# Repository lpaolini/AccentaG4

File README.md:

# AccentaG4
Virtual keypad for Honeywell Security Accenta G4 panel.

## Introduction
[Accenta G4](https://www.security.honeywell.com/uk/products/intruder/control-panels/gen4/) is a simple, reliable, affordable intruder alarm panel made by *Honeywell Security*.

It works very well for residential use but, clearly, it’s not designed for extension. You cannot expand zones, you can’t operate it remotely with your smartphone, it doesn’t expose a standard serial interface to play with.

Recently, I started dreaming of a more sophisticated panel, and after thinking of a possible upgrade, I decided to hack mine.

After a bit of googling, I found a blog with a couple of interesting posts ([this](https://inmachinablog.wordpress.com/2015/11/04/accenta-alarm-keypad-protocol/) and [this](https://inmachinablog.wordpress.com/2015/11/03/decoding-the-alarm-keypad-protocol/)) providing useful background on the protocol and signalling used on the keypad bus, along with a description of the messages exchanged between the keypad and the panel.

## Keypad bus

The keypads (in [LED](https://www.security.honeywell.com/uk/products/intruder/control-panels/gen4/462382.html) and [LCD](https://www.security.honeywell.com/uk/products/intruder/control-panels/gen4/462383.html) variants) communicate with the panel over a single wire (half-duplex, shared bus) using TTL levels (+5v low, 0v high). A quick analysis with the logic analyzer revealed a slightly unusual protocol: RS-232 with 8 bit of data, *mark/space parity* and 1 stop bit or, if you prefer, *9 bit* of data and 1 stop bit, which is the same. In fact, considering bits are sent LSB first (little-endian), the parity bit is just the 9th bit of data.

Any message is sent over the bus with mark parity on the first byte and space parity on the remaining bytes.

## Messaging protocol

Luckily, all communication between panel and keypads is not encrypted nor obfuscated. In fact, the protocol is fairly straightforward.
Any message consists of a single byte command, one or more bytes of data and a one-byte checksum of all the preceding bytes.
Messages are not terminated.
```
<command> <data> [<data>...] <checksum>
```
### Messages sent by the keypad

Apparently, the keypad sends just one type of command over the bus:
```
K <keycode> <checksum>
```
The “K” character, being the first byte of the message, has mark parity.

\<keycode\> is the code representing a physical or virtual (key combination) button on the keypad:

| code | ASCII | type     | button  |
| ---- | :---: | -------- | :-----: |
| 0x30 | 0     | physical | 0       |
| 0x31 | 1     | physical | 1       |
| 0x32 | 2     | physical | 2       |
| 0x33 | 3     | physical | 3       |
| 0x34 | 4     | physical | 4       |
| 0x35 | 5     | physical | 5       |
| 0x36 | 6     | physical | 6       |
| 0x37 | 7     | physical | 7       |
| 0x38 | 8     | physical | 8       |
| 0x39 | 9     | physical | 9       |
| 0x3a | :     | physical | chime   |
| 0x3b | ;     | physical | omit    |
| 0x3c | <     | physical | cancel  |
| 0x3d | =     | physical | program |
| 0x3e | >     | physical | confirm |
| 0x3f | ?     | physical | select  |
| 0xaa | n/a   | virtual  | panic   |

### Messages sent by the panel

The panel sends out one or more messages whenever it needs to update the status displayed on the keypads. Messages of a given type are sent only if they differ from the previous message of the same type.

Please note some responses are sent exclusively as audible tones, delivered as analogue signals via a separate keypad bus wire labeled *SOUNDS*.

#### Messages for the LED keypad (P)

Whenever the status of at least one of the LEDs needs to be updated, a new message is sent.
Each message is a *full* representation of all the LEDs on the keypad.
```
P <zone info> <general info> <checksum>
```
The “P” character, being the first byte of the message, has mark parity.

\<zone info\> is a byte where each bit represents one zone LED:

| bit | LED |
| :-: | --- |
| 0   | zone 1 |
| 1   | zone 2 |
| 2   | zone 3 |
| 3   | zone 4 |
| 4   | zone 5 |
| 5   | zone 6 |
| 6   | zone 7 |
| 7   | zone 8 |

\<general info\> is a byte encoded like follows:

| bit | LED |
| :-: | --- |
| 0   | system unset |
| 1   | tamper |
| 2   | SOS |
| 3   | power |
| 4   | not used? |
| 5   | not used? |
| 6   | not used? |
| 7   | not used? |

#### Messages for the LCD keypad (L)

Whenever the text displayed on the LCD needs to be updated a new message is sent:
```
L <lenght> <LCD data> <checksum>
```
The “L” character, being the first byte of the message, has mark parity.

Lenght information is necessary, as messages are not terminated and size is not fixed, thus the receiver needs to know the message size upfront.

LCD data is a sequence of bytes, either printable (ASCII) or control codes, mostly for managing the cursor:

| code | function |
| ---- | -------- |
| 0x04 | cursor position |
| 0x05 | hide cursor |
| 0x06 | show cursor |
| 0x07 | move cursor right |
| 0x0a | newline |
| 0x0c | clear |
| 0x10 | unknown |
| 0x16 | unknown | 

Cursor position is determined by the subsequent byte:

| position | coordinates |
| -------- | ----------- |
| 0x80 to 0x8f | top row, column 1 to 16 |
| 0xc0 to 0xcf | bottom row, column 1 to 16 |

I believe the LCD keypad consumes "P" messages as well, as information regarding the status of the *power* and *day* LEDs doesn't seem to be show up anywhere in "L" messages.

## To parity or not to parity…

As said, in little-endian, 8-bit with parity and 9-bit without parity are equivalent.

In particular, 8-bit with mark parity is equivalent to 9-bit without parity when the 8-bit character is *OR*ed with 0x100.

So, it’s perfectly equivalent to forget about parity and simply think of alternate codes for the head of the message, with the 9th (or parity) bit set to 1:

| command | keycode | 9-bit code |
| :-----: | :-----: | :--------: |
| K       | 0x4b    | 0x14b      |
| L       | 0x4c    | 0x14c      |
| P       | 0x50    | 0x150      |

No matter how you look at it, having the 9th bit set exclusively for the head of the message is quite convenient, as it makes the code at the receiving end simpler and more robust. In fact it's possible to detect the head of the message without any ambiguity.

## Hardware signals

Keypad bus aside, the panel board exposes also a few output signals representing the general status, for use with a digital communicator or a speech dialer. They are labelled as follows:

- FIRE (fire)
- PA (panic)
- INT (intruder)
- SET (alarm set)
- ABORT (alarm aborted)

Signals are held at +13v and fall to 0v when active.
They are absolutely crucial for this project as some critical alert conditions (like *intruder* or *PA*) are not reflected in LED or LCD status.

## The project

The objective of this project is to build a keypad emulator running in a standard browser.

# Hardware stack

## Linux MPU: [Raspberry Pi 3+](https://www.raspberrypi.org/products/raspberry-pi-3-model-b-plus/)

The MPU is responsible for the following tasks:

- expose a HTTPS server for serving the web application
- expose a secure websockets server (used by the web application)
- accept and manage websockets connections
- listen to MCU for incoming messages and broadcast to websockets clients
- listen to websockets clients for incoming messages and forward to MCU
- send email notifications

[Server-side code](src/mpu/server) is written in Javascript and runs under latest NodeJS and depends on [express](https://github.com/expressjs/express) [serialport](https://github.com/serialport/node-serialport), [ws](https://github.com/websockets/ws) and [rxjs](https://github.com/ReactiveX/rxjs)

[Client-side code](src/mpu/client) is a HTML5/CSS3/Javascript application running in the browser.

## Arduino MCU: [Watterott RPI-UNO-HAT](https://learn.watterott.com/hats/rpi-uno-hat/)

[RPI-UNO-HAT](https://shop.watterott.com/RPi-UNO-HAT-Raspberry-Pi-Arduino-Erweiterung_1) is a very nice Raspberry Pi HAT fully compatible with Arduino UNO. It features standard headers and serial communication between Raspberry Pi and Arduino, so it's possible to program and reset the Atmel MCU from the Raspberry.

In practice, Raspberry Pi + RPI-UNO-HAT = **Arduino Yún on steroids**!

The MCU is responsible for the following tasks:

- monitor Accenta G4 panel hardware signals (PA, INT, SET, ABORT), update local state and send updates to MPU
- provide bidirectional serial connectivity with Accenta G4 keypad bus
- listen to the keypad bus for incoming messages, update local state and send updates to MPU
- listen to MPU for virtual keystrokes and send emulated keypad messages over the keypad bus
- listen to MPU for status queries and send local status
- reply to heartbeat messages to be broadcasted to the clients, to prove end-to-end connection is alive

[Arduino code](src/mcu/HomeControl) is written in C/C++ and it's built around the [SoftwareSerial9](https://github.com/lpaolini/SoftwareSerial9) library, capable of sending and receiving 9-bit messages, and [QueueArray](http://playground.arduino.cc/Code/QueueArray), a FIFO library used for enqueuing and throttling outgoing commands.

**WARNING**: the original version of SoftwareSerial9 by [addible](https://github.com/addibble/SoftwareSerial9) had a bug in the recv() method, fixed by [edreanernst](https://github.com/edreanernst/SoftwareSerial9) in his fork, then fixed by addible too. Both work fine, just make sure to use the latest version.

## Custom hardware

Interfacing the panel with Arduino is pretty simple.

In theory, two digital I/O pins and a diode is all you need for connecting the single-wire keypad bus to distinct RX and TX ports.

In practice, adding an additional resistor and a zener diode is a safe choice for limiting voltage and current across Arduino's I/O pins.

Panel signals (SET, ABORT, INT, PA) are active-low (12v on, 0v on). If Arduino's input is configured as INPUT_PULLUP, a diode is enough to pull the input down to LOW logical level when the corresponding panel output is active (LOW).

However, the keypad bus might be tampered with or be subject to interferences potentially harmful to Arduino. For these reasons, I have designed an opto-isolated circuit which provides full electrical isolation between Arduino and the panel itself.

 keypad bus and panel signals interface")

The circuit is designed to keep the opto-isolator LEDs off during standby, to maximize their life expectancy. 
Here is a short description of the resistors:

|Resistor|Description|
|:------:|-----------|
|R1      |limit the current into the transmitting opto-isolator LED|
|R2      |limit the current into the transmitting opto-isolator transistor|
|R3      |limit the current into the receiving opto-isolator transistor|
|R4      |limit the current into the receiving opto-isolator LED|
|R5      |set the saturation current for T2|
|R6      |set the saturation current for T1|

TO BE CONTINUED...

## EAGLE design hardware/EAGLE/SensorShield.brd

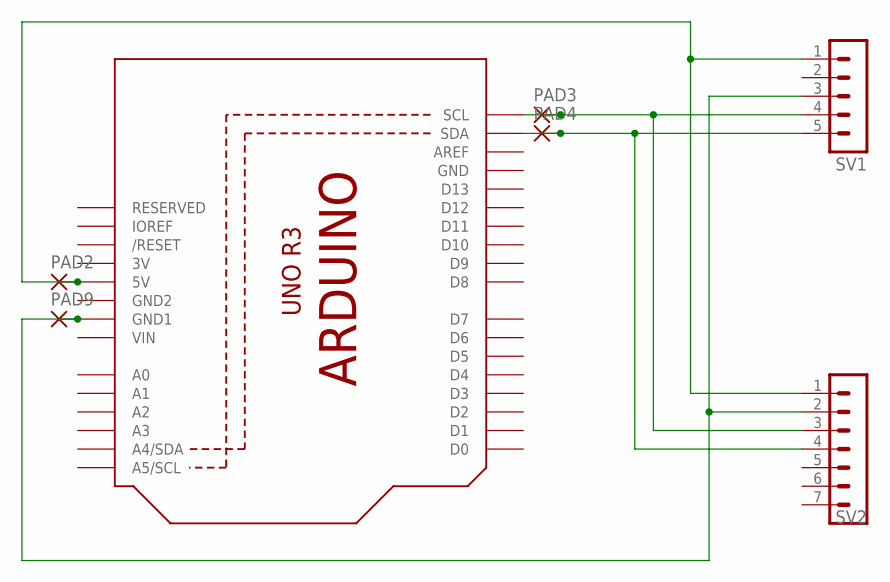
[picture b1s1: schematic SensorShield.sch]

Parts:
PAD2, PAD3, PAD4, PAD9: 1,6/0,8
SV1: MA05-1
SV2: MA07-1
U1: ARDUINOR3-BPLACE

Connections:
3V: U1.3V
GND: U1.GND
GND2: U1.GND2
unnamed: PAD9.1, SV1.3, SV2.2, U1.GND1
unnamed: PAD3.1, SV1.4, SV2.3, U1.SCL
unnamed: PAD4.1, SV1.5, SV2.4, U1.SDA
unnamed: PAD2.1, SV1.1, SV2.1, U1.5V
VIN: U1.VIN

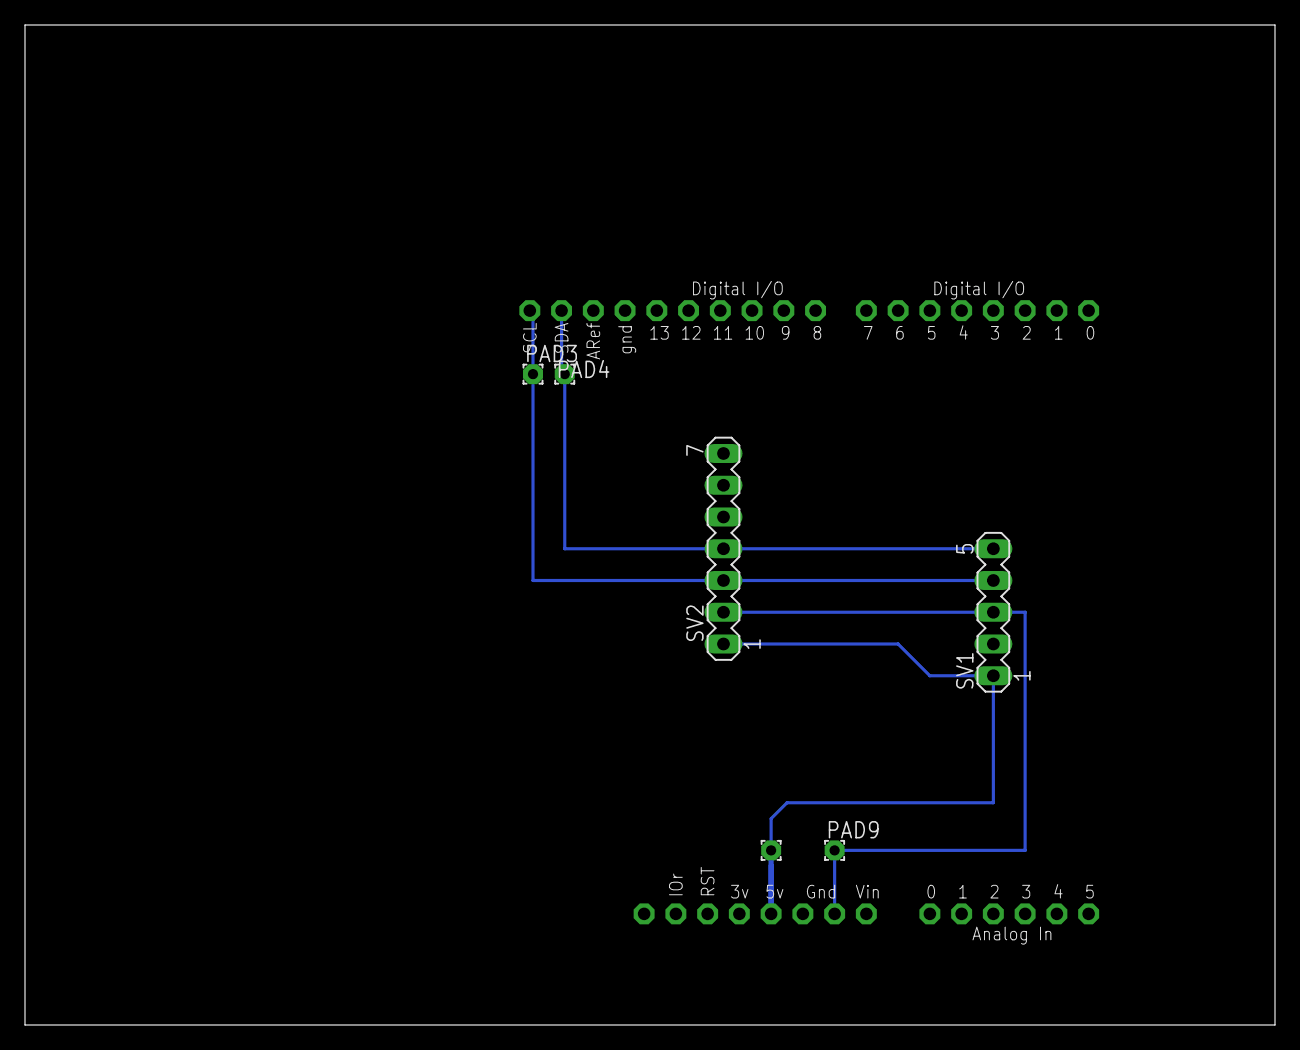
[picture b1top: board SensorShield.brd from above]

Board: 2 copper layers, 100.0 x 80.0 mm, 7 parts (0 on the bottom side), 4 nets.

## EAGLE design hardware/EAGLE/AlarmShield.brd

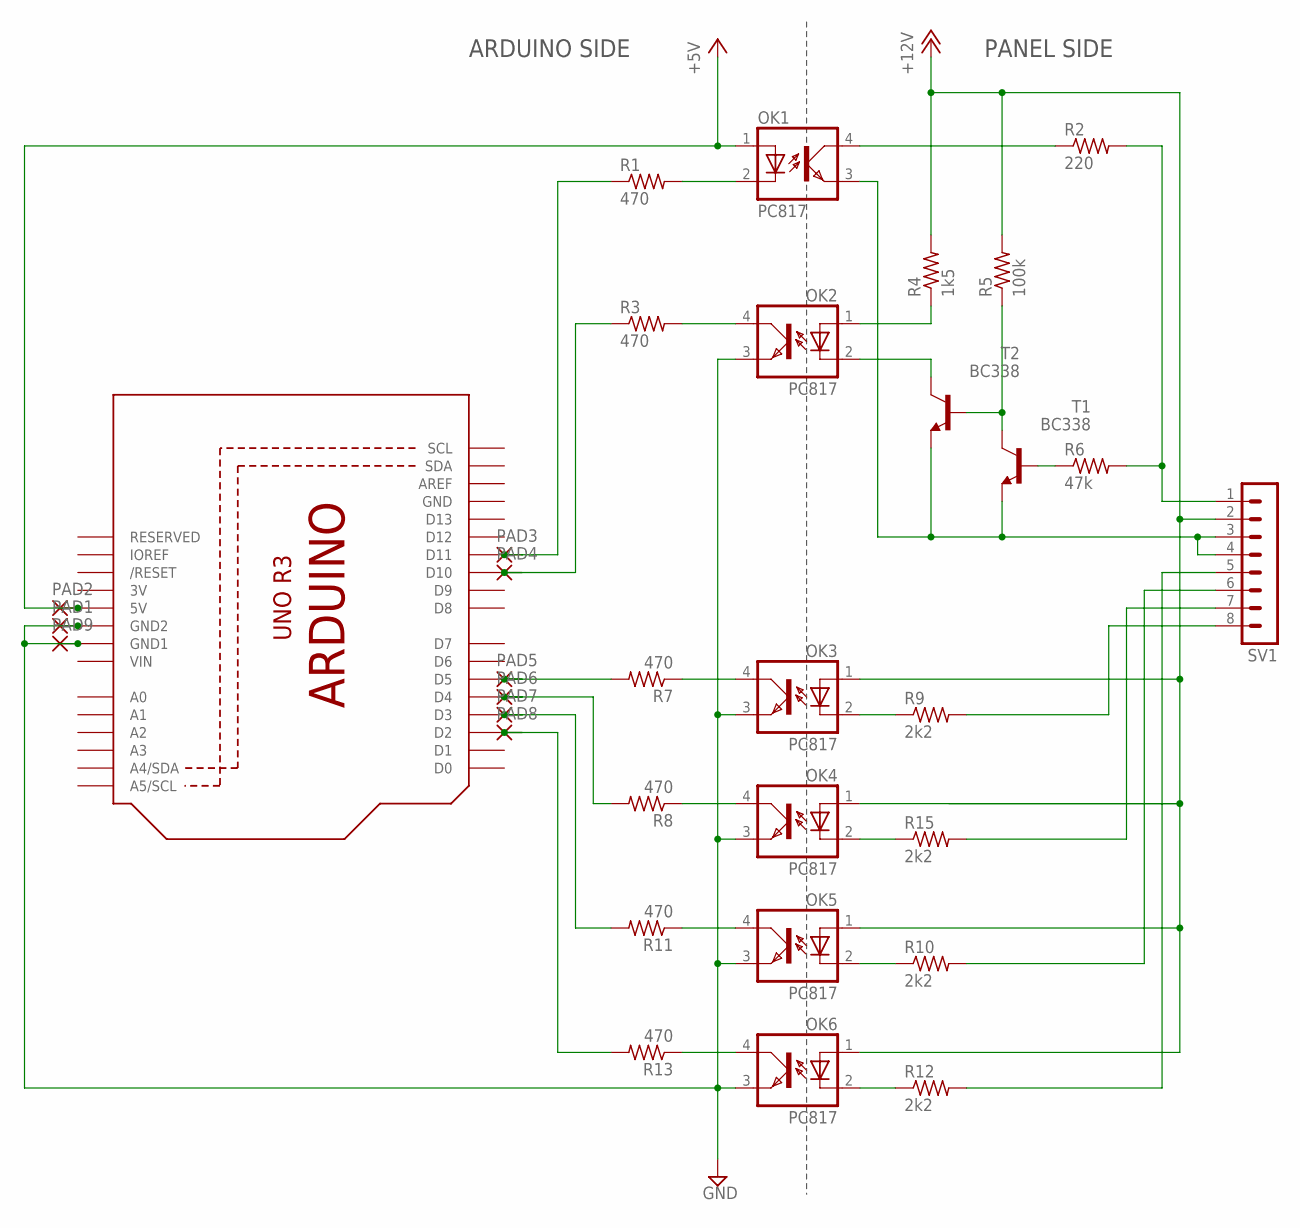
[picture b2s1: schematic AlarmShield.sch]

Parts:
OK1, OK2, OK3, OK4, OK5, OK6: PC817; DIP4
PAD1, PAD2, PAD3, PAD4, PAD5, PAD6, PAD7, PAD8, PAD9: 1,6/0,8
R1, R3, R7, R8, R11, R13: 470; 0207/10
R2: 220; 0207/10
R4: 1k5; 0207/10
R5: 100k; 0207/10
R6: 47k; 0207/10
R9, R10, R12, R15: 2k2; 0207/10
SV1: MA08-1
T1, T2: BC338; TO92-EBC
U1: ARDUINOR3-BPLACE

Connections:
3V: U1.3V
+5V: OK1.1 (A), PAD2.1, U1.5V
+12V: OK3.1 (A), OK4.1 (A), OK5.1 (A), OK6.1 (A), R4.2, R5.2, SV1.2
GND: U1.GND
GND1: OK2.3 (EMIT), OK3.3 (EMIT), OK4.3 (EMIT), OK5.3 (EMIT), OK6.3 (EMIT), PAD1.1, PAD9.1, U1.GND1, U1.GND2
unnamed: OK1.2 (C), R1.2
unnamed: OK1.3 (EMIT), SV1.3, SV1.4, T1.E, T2.E
unnamed: OK1.4 (COL), R2.1
unnamed: OK3.4 (COL), R7.1
unnamed: OK4.4 (COL), R8.1
unnamed: OK2.1 (A), R4.1
unnamed: OK2.2 (C), T2.C
unnamed: R5.1, T1.C, T2.B
unnamed: PAD3.1, R1.1, U1.D11
unnamed: R6.1, T1.B
unnamed: OK5.4 (COL), R11.1
unnamed: PAD5.1, R7.2, U1.D5
unnamed: OK6.4 (COL), R13.1
unnamed: OK2.4 (COL), R3.2
unnamed: PAD6.1, R8.2, U1.D4
unnamed: PAD7.1, R11.2, U1.D3
unnamed: PAD4.1, R3.1, U1.D10
unnamed: R2.2, R6.2, SV1.1
unnamed: R9.2, SV1.8
unnamed: R15.2, SV1.7
unnamed: OK4.2 (C), R15.1
unnamed: PAD8.1, R13.2, U1.D2
unnamed: R10.2, SV1.6
unnamed: OK3.2 (C), R9.1
unnamed: R12.2, SV1.5
unnamed: OK5.2 (C), R10.1
unnamed: OK6.2 (C), R12.1
VIN: U1.VIN

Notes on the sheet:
PANEL SIDE
ARDUINO SIDE

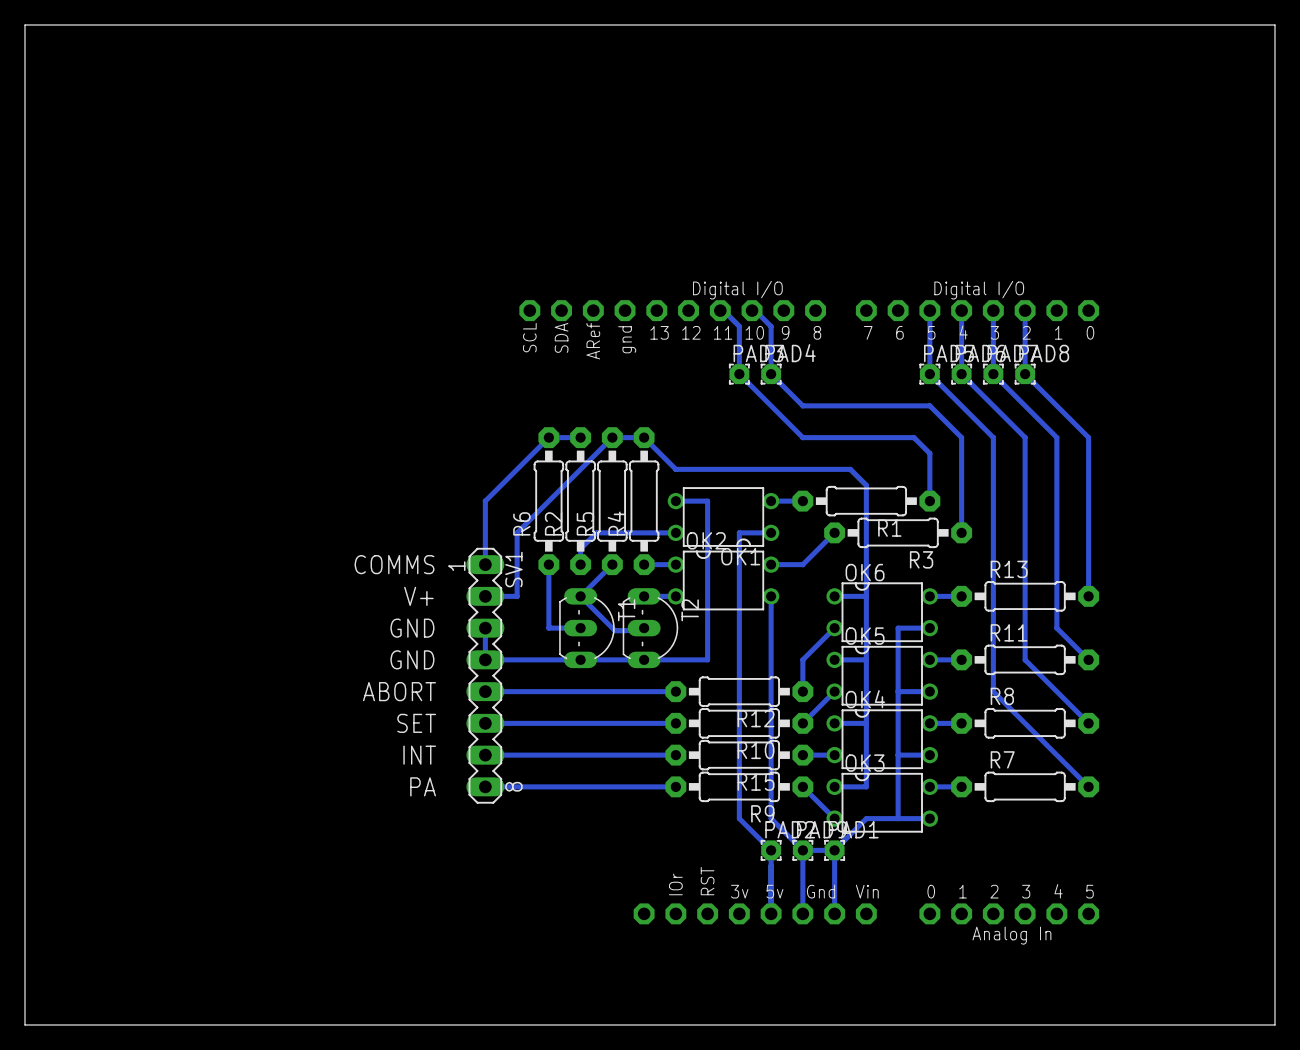
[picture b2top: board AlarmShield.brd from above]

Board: 2 copper layers, 100.0 x 80.0 mm, 33 parts (0 on the bottom side), 30 nets.

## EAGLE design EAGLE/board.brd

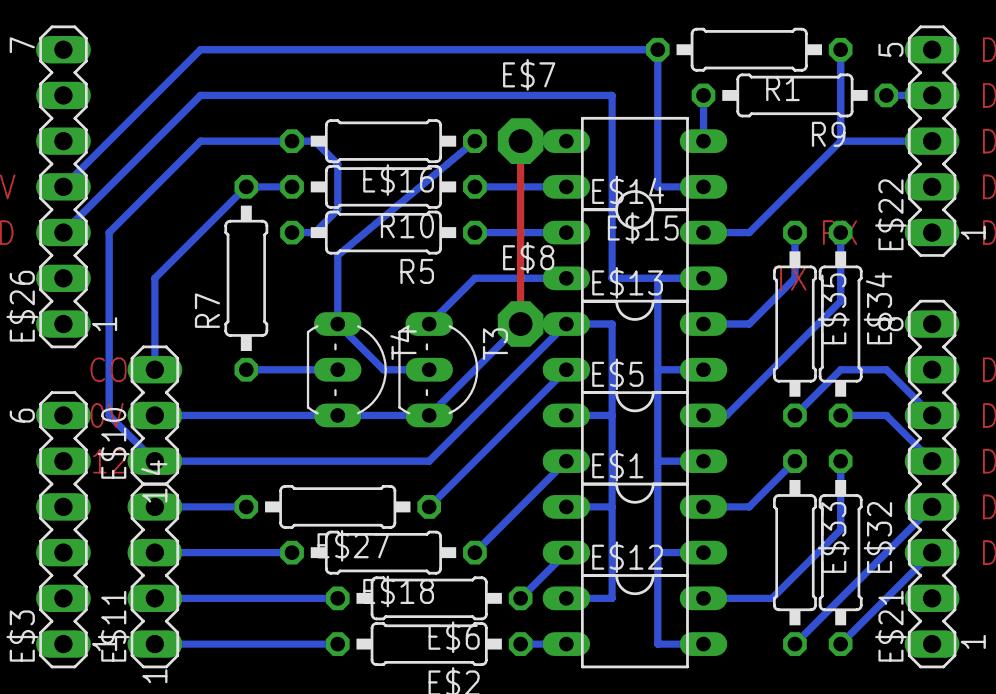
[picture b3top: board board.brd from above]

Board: 2 copper layers, 30 parts (0 on the bottom side), 12 nets.

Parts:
E$1, E$5, E$12, E$13, E$14, E$15: DIL04
E$2, E$6, E$18, E$27: 2k2; 0207/10
E$3: MA06-1
E$7, E$8: PAD-01
E$10: MA03-1
E$11: MA04-1
E$16: 100k; 0207/10
E$21: MA08-1
E$22: MA05-1
E$26: MA07-1
E$32, E$33, E$34, E$35: 820; 0207/10
R1: 4k7; 0207/10
R5: 1k2; 0207/10
R7: 47k; 0207/10
R9: 390; 0207/10
R10: 220; 0207/10
T3, T4: TO92-CBE

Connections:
S$6: R7.1, T4.B
S$10: E$21.3, E$32.2
S$11: R7.2, R10.2
S$12: E$22.4, R9.1
S$13: E$22.3, R1.1
S$15: E$16.1, T3.B, T4.C
S$16: E$21.4, E$33.2
S$19: E$21.5, E$34.2
S$20: E$14.2, T3.C
S$21: E$21.6, E$35.2
S$28: E$10.2, T3.E, T4.E
S$55: E$10.1, E$16.2, R5.2

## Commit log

2017-05-02 initial import
2017-05-02 refactoring and polishing
2017-05-02 fix flashing background alert
2017-05-02 remove unnecessary conversion
2017-05-02 fix int to char cast
2017-05-03 refactoring
2017-05-03 fix size for lcd status variable
2017-05-03 gitignore .hex files
2017-05-03 set encoding to binary (default is utf-8)
2017-05-03 fix splitting of received messages
2017-05-03 implement basic LCD functionality
2017-05-03 increase message max length to 50
2017-05-03 bugfix: remove unwanted call to sendCommands()
2017-05-03 add serial monitoring of received messages
2017-05-03 add more logging
2017-05-03 add ready message
2017-05-03 trying to fix lost L messages
2017-05-04 bugfix: stop listening to software serial when transmitting (some incoming chars were missing)
2017-05-04 fix cursor right control code
2017-05-04 implement select button
2017-05-04 refactoring, cleanup
2017-05-04 reimplement user interface layout to fit SEL button
2017-05-05 cleanup
2017-05-05 implement flashing cursor
2017-05-05 reset lcd on connection lost
2017-05-05 Set theme jekyll-theme-cayman
2017-05-05 documentation images
2017-05-05 move EAGLE files into hardware directory
2017-05-06 implement MCU heartbeat
2017-05-08 add cases for unknown control chars, handle websocket closed
2017-05-08 implement two levels of heartbeat
2017-05-08 fix heartbeat timing
2017-05-08 comment-out unknown cases
2017-05-08 improve heartbeat
2017-05-09 implement websocket connection timeout and autorestart
2017-05-09 improve visibility
2017-05-10 refine colors
2017-05-10 improve resilience to dropped connection
2017-05-10 fix notifications
2017-05-13 harden monitor
2017-06-08 inherit ws server from current uri
2017-06-08 implement secure websockets
2017-06-08 fix ssl cert path
2017-06-08 implement both SSL and standard websockets
2017-06-15 keep track of last status update
2017-06-20 make SSL key and certificate configurable
2017-06-21 reimplment circuit shield
2017-06-21 fix websocket path
2017-06-21 make config file parametric
2017-06-23 add favicon
2017-06-23 serve jquery and jquery-visibility from cloudflare
2017-06-23 serve jquery from google cdn
2017-06-24 use pointer cursor for clickable items
2017-06-24 animate buttons when pressed
2017-06-25 hide chrome touch highlight
2017-06-29 monitor link status
2017-07-01 change orientation to portrait
2017-07-03 remove support for non-secure websocket
2017-07-08 change viewport size
2017-07-11 ignore .vscode directory
2017-07-17 switch from ssmtp to mstmp
2017-07-24 increase keypress delay to 200ms
2017-07-25 adjust keypress delay to 150ms
2017-07-25 improve alarm background flashing
2017-07-25 update schematics
2017-07-26 fix wrong regex
2017-07-26 filter printable lcd chars
2018-01-12 SoftwareSerial9 now fixed by addible
2018-05-17 removed support for landscape mode
2018-05-17 added P1, P2, P3 and PANIC buttons
2018-05-17 reimplemented layout using flexes
2018-05-17 Implemented LCD offline message
2018-05-21 Add compiled binary.
2019-03-29 Moved heartbeat functionality to main.
2019-03-29 Cleanup.
2019-03-30 Used String for messages.
2019-03-30 Implemented basic AirSensor class.
2019-03-30 Reformatted code.
2019-04-03 Reimplementing.
2019-04-03 Refactored.
2019-04-04 Replaced single-char op codes with three-char.
2019-04-04 Implementing air quality display.
2019-04-05 Added eslint configuration.
2019-04-05 Cleanup (eslint).
2019-04-05 Added eslint configuration (client).
2019-04-06 Minor optimizations.
2019-04-06 Added main loop led confirmation.
2019-04-06 Minor performance optimization.
2019-04-07 Reimplemented SHT31 sensor using ClosedCube library.
2019-04-13 Added sensor shield board.
2019-05-01 Added SGP30 initialization.
2019-05-01 Added check for handler and read method.
2019-05-01 Added support for configurable arm/disarm hour.
2019-05-01 Replaced startsWith with substring.
2019-05-01 Implementing arm/disarm UI.
2019-05-01 Fixed typo.
2019-05-05 Refactoring.
2019-09-27 Porting to Raspberry Pi.
2019-09-27 Reimplementing with rxjs.
2019-09-28 Reimplementing heartbeats to prevent serial interferences during boot.
2019-09-28 Reimplemented SerialBridge.
2019-09-28 Reimplemented heartbeat handling.
2019-09-28 Implemented handleHeartbeat function.
2019-09-28 Re-enabled sensors.
2019-09-29 Updated client libraries, added rxjs.
2019-09-29 Refactoring client.
2019-10-01 Implemented display of air parameters.
2019-10-01 Implemented start/stop of sensors on communication enable/disable.
2019-10-01 Changed SHT31 reading mode to periodic.
2019-10-01 Fixed error check.
2019-10-01 Switched from ClosedCube to Adafruit SHT31 library.
2019-10-01 Changed precision of humidity readings.
2019-10-01 Removed absolute humidity.
2019-10-01 Implemented queryStatus() for sensors.
2019-10-13 Changed websocket port to 10444.
2019-11-04 Implemented node.js server for serving client files.
2019-11-04 Added default route.
2019-11-04 Disabled logging.
2020-01-03 Replaced msmtp with sendmail.
2020-01-10 Synchronized led blink to heartbeat.
2020-01-27 Added missing main envelope 'From' line.
2020-02-22 Removed 'enable' signal throttling.
2020-03-15 Git ignored node_modules.
2020-03-15 Implemented log4js.
2020-03-15 Removed log4js.
2020-03-15 Improved logging.
2020-03-15 Fixed millis() rollover.
2020-03-15 Fixed compilation warnings.
2020-03-15 Recompiled.
2020-08-03 Implementing days.
2020-08-03 Fixed joining of days.
2020-08-03 Fixing day.s
2020-08-03 Fixed assignment to const.
2020-08-03 Fixed days.
2020-08-03 Fixed display of days.
2020-08-05 Reimplemented status as event emitter.
2020-08-05 Fixed events.
2020-08-05 Changed intruder/panic messages.
2020-08-05 Updated deactivation messages.
2021-04-19 Adjusted monospace font size.
2021-05-06 Adding arm/disarm toggle.
2021-08-30 Updated npm packages.
2021-08-30 Fixing.
